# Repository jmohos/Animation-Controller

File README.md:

# Animation-Controller
Robotic Animation Control Project

## VS Code Workspace
Use the workspace file when building, uploading, or monitoring the serial port so VS Code opens the full project with PlatformIO settings.

Prerequisites:
- Visual Studio Code
- PlatformIO IDE extension for VS Code (installs toolchains and dependencies on first build)
- Teensy 4.1 USB drivers for your OS (Windows: Teensyduino installer includes the driver)
- A known-good USB data cable for upload and serial monitoring

1. Open VS Code.
2. File -> Open Workspace from File...
3. Select `2025_Animation_Controller.code-workspace` in the repo root.
4. Use the PlatformIO toolbar to Build, Upload, and Monitor the serial port.
5. First build: PlatformIO will download toolchains and libraries. Select the Teensy serial port and use 115200 baud for the monitor.

## Display
The control station software currently targets the ILI9341 240x320 display only.
Other display drivers and build options have been removed.

## Functional System Description
To faciliate the orchestration of an animated robotic system, an animation controller assembly is needed.  This controller takes on the responsibility of monitoring and controlling all participating show elements in a synchronized manner.  A typical parade float can consist of a dozen animated features that each require managed motion across potentially multiple dimensions.  By having a single control node manage all of the animated features, all of the elements can be synchronized into a cohesive show where coordinated motion can add to the quality of the performance. This project covers the design of such an animation controller.

The key high level requirements include:
* A single control assembly that can operate on 12VDC power input.
* Has a user interface for the local animation operator to monitor the overall animation, control the selected animation process, manually control elements and edit the animation sequence.
* Can control a series of robotic endpoints using one CAN bus plus up to 7 full-duplex serial ports (Serial1 pins 0/1 reserved for CAN).
* Robotic endpoints can be either motion, light or sound controllers.
* The motion control endpoints will include the BasicMicro Roboclaw controllers which can control either 1 or 2 motors via a single serial interface.
* RoboClaw controllers must be configured for Packet Serial mode at 115200 baud.
* Future options for motion control endpoints will include options to manage stepper motors, servos, solenoids and hydraulic valves.
* Future options for light control will include endpoints to manage DMX-based light controllers.
* Future options for sound control will include endpoints that can receive commands to play audio tracks.
* Animation sequences shall be stored in a portable animation sequence file that contains the time-based steps for each animation endpoint.
* Animation sequences are stored on the animation controller SD card.

## Endpoint and Animation Files
Endpoint configuration lives in `/endpoints.csv` on the SD card. The animation sequence lives in `/animation.csv` and only contains a `[sequence]` section. The animation file defines a single looping animation with a maximum duration of 5 minutes (300000 ms).

Endpoint config schema (CSV columns, in order):
1. `endpoint_id` - 1-based endpoint index.
2. `type` - `ROBOCLAW`, `MKS_SERVO`, `REV_FRC_CAN`, `JOE_SERVO_SERIAL`, or `JOE_SERVO_CAN`.
3. `address` - Device address or CAN ID (hex allowed, e.g. `0x80`).
4. `enabled` - `1` or `0`.
5. `position_min` - Minimum allowed position (degrees if `pulses_per_rev > 0`, else device units).
6. `position_max` - Maximum allowed position (degrees if `pulses_per_rev > 0`, else device units).
7. `velocity_min` - Minimum allowed velocity (deg/s if `pulses_per_rev > 0`, else device units).
8. `velocity_max` - Maximum allowed velocity (deg/s if `pulses_per_rev > 0`, else device units).
9. `accel_min` - Minimum allowed acceleration (deg/s² if `pulses_per_rev > 0`, else device units).
10. `accel_max` - Maximum allowed acceleration (deg/s² if `pulses_per_rev > 0`, else device units).
11. `serial_port` - Interface index (0=CAN on pins 0/1, 1-7=RS422 serial ports).
12. `motor` - RoboClaw motor channel (`1` or `2`), `0` when unused.
13. `pulses_per_rev` - Pulses per revolution for engineering units (0 = device units mode, >0 enables degrees/deg/s units).
14. `home_offset` - Offset from limit switch to zero position in pulses.
15. `home_direction` - Homing direction (0=negative, 1=positive).
16. `has_limit_switch` - Limit switch present (0=no, 1=yes).

Sequence schema (CSV columns, in order):
1. `time_ms` - Integer milliseconds from 0 to 300000.
2. `endpoint_id` - 1-based endpoint index.
3. `position` - Target position.
4. `velocity` - Target velocity.
5. `accel` - Target acceleration.
6. `mode` (optional) - `pos` (default) or `vel` to issue a velocity-only command.

Example:
```
# endpoints.csv
# endpoint_id,type,address,enabled,position_min,position_max,velocity_min,velocity_max,accel_min,accel_max,serial_port,motor,pulses_per_rev,home_offset,home_direction,has_limit_switch
1,MKS_SERVO,0x00000001,1,-360,360,0,100,0,50,0,0,16384,0,0,0
2,ROBOCLAW,0x00000080,1,-360,360,0,100,0,50,1,1,4096,0,0,0

# animation.csv
[sequence]
# time_ms,endpoint_id,position,velocity,accel,mode
0,1,0,800,250,pos
2000,1,1000,800,250,pos
```

Notes:
- Lines starting with `#` are comments and ignored.
- The animation loops at the largest `time_ms` found, capped at 300000 ms.
- `velocity` and `accel` are required on every row for consistency.
- Serial1 (pins 0/1) is reserved for the CAN transceiver and is not available for RS422 endpoints.
- The CAN bus is initialized at 500 kbps.
- Default SD card files live in `Software/Animation_Control_Station/sd_defaults`.

## Known Issues

### CAN Bus Interrupt Mode
The CAN bus currently operates in **polled mode only**. Interrupt mode causes system crashes on Teensy 4.1. This is a known issue with the FlexCAN_T4 library or hardware timing.

**Workaround**: The code uses `CANBUS_USE_POLLING` (defined by default). The `CanBus::events()` method explicitly reads the mailbox each loop iteration. Performance impact is minimal at 500 kbps.

**Status**: Under investigation. Do not enable `CANBUS_USE_INTERRUPTS`.

### EEPROM Configuration Migration
Upgrading from firmware versions with config version < 7 will reset endpoint configuration to defaults. After upgrading, reload your `/endpoints.csv` file from SD card.

## Troubleshooting

### CAN Bus Issues
- **Symptom**: MKS Servo not responding
- **Check**: Verify CAN transceiver connected to Teensy pins 0 (CAN_TX) and 1 (CAN_RX)
- **Check**: Verify 500 kbps bitrate match on all devices
- **Check**: CAN bus requires 120Ω termination resistors at both ends
- **Debug**: Use console command `can status` to check error counters

### SD Card Not Detected
- **Symptom**: "SD card not ready" message on boot
- **Check**: SD card must be formatted as FAT32
- **Check**: Verify `/endpoints.csv` and `/animation.csv` exist in root directory
- **Check**: Use known-good SD card (some cards have compatibility issues)
- **Recovery**: Copy files from `sd_defaults/` directory

### RoboClaw Not Responding
- **Symptom**: No motion from RoboClaw-controlled motors
- **Check**: RoboClaw must be in **Packet Serial mode** at 115200 baud
- **Check**: Verify RS422 serial connections (TX/RX not swapped)
- **Check**: Verify RoboClaw address matches `endpoints.csv` configuration
- **Debug**: Use console command `rc status <endpoint_id>` to read encoder values

### Encoder Position Drift
- **Symptom**: Position drifts over time or after power cycle
- **Solution**: Perform homing sequence with `home <endpoint_id>` command
- **Check**: Verify limit switches are properly wired and configured
- **Check**: Verify `has_limit_switch=1` in endpoints.csv for endpoints that support homing

## Engineering Units System

Starting with firmware version 7, the system supports **engineering units** for position, velocity, and acceleration commands. This allows you to specify motion in degrees and degrees per second regardless of the underlying hardware.

### Configuration

Set the `pulses_per_rev` field in `/endpoints.csv` to enable engineering units for an endpoint:

```csv
endpoint_id,type,address,...,pulses_per_rev,home_offset,home_direction,has_limit_switch
1,MKS_SERVO,0x00000001,...,16384,0,0,0
```

**Pulses Per Revolution Values**:
- **MKS Servo**: 16384 pulses/revolution (encoder subdivisions, default)
- **RoboClaw**: Depends on encoder resolution and gearing (e.g., 4096 for common encoders)
- **Custom**: Calculate as: `encoder_lines * 4 * gearing_ratio * microstepping`

**Important**: The `pulses_per_rev` value must account for:
1. Encoder resolution (quadrature count = 4× encoder lines)
2. Microstepping (if applicable)
3. Gearing between motor shaft and final output shaft

### Units

When `pulses_per_rev > 0`, all position/velocity/acceleration values use engineering units:

| Parameter | Units | Range | Notes |
|-----------|-------|-------|-------|
| **Position** | degrees | ±2,000,000° | Multi-revolution support (±5,555 revs) |
| **Velocity** | deg/s | 0-360 deg/s typical | Converts to RPM for MKS, counts/s for RoboClaw |
| **Acceleration** | deg/s² | 0-100 deg/s² typical | Converts to device-specific scale |

### Examples

**360° rotation at 60 RPM**:
```csv
[sequence]
time_ms,endpoint_id,position,velocity,accel,mode
0,1,0,360,50,pos
1000,1,360,360,50,pos
```

**Continuous rotation**:
```csv
0,1,0,180,50,pos
2000,1,720,180,50,pos     # 2 full revolutions
4000,1,1440,180,50,pos    # 4 full revolutions
```

### Backwards Compatibility

To maintain device units (old behavior), set `pulses_per_rev = 0` in endpoints.csv. The system will pass position/velocity/acceleration values directly to the hardware without conversion.

### Homing and Zero Position

The system supports auto-homing with limit switches:

1. Set `has_limit_switch=1` in endpoints.csv
2. Set `home_direction` (0=negative, 1=positive)
3. Set `home_offset` (distance in pulses from limit to zero position)
4. Run homing: Console command `home <endpoint_id>` or use Homing screen

After homing, all position commands are relative to the zero position.

## Console Commands Reference

Connect via USB serial at 115200 baud. Commands are case-sensitive.

### SD Card Commands
- `sd dir` - List files on SD card
- `sd read <path>` - Display file contents
- `sd test` - Test SD card read/write performance

### Configuration Commands
- `config save` - Save current configuration to EEPROM
- `config load endpoints` - Reload `/endpoints.csv` from SD card
- `config show` - Display current configuration
- `factory reset` - Reset to factory defaults (WARNING: erases config)

### Endpoint Commands
- `ep list` - Show all endpoint configurations
- `ep show <id>` - Show detailed config for endpoint
- `ep enable <id>` - Enable endpoint
- `ep disable <id>` - Disable endpoint

### Sequence Commands
- `seq load` - Reload `/animation.csv` from SD card
- `seq info` - Display sequence statistics (event count, duration)

### RoboClaw Commands
- `rc status <endpoint_id>` - Read encoder position and speed

### CAN Bus Commands
- `can status` - Display CAN bus health (error counters, fault state)

### Homing Commands
- `home <endpoint_id>` - Start auto-homing sequence for endpoint

### System Commands
- `reboot` - Restart controller
- `help` - Display command list

### Hardware - Overall System
The animator controller is the heart of a complete animation deployment used for shows like parade floats and general animatronic performances.  Such shows require multiple robotic actuators to work independently or in concert to perform synchronized motion, light and sound sequences.

A deployed system would typically consist of:
* Robotic power system to provide electrical power to the animation controller, motion controllers, lights and sound systems.
* A robotic animation controller to manage the entire show process.  This controller would contain a scripted set of animations to orchestrate across all of the animated elements.
* A set of robotic endpoints that the animation controller manages.  Each of these endpoints communicates with the animation controller via a serial link.  Endpoints report their status and receive control commands from the animation controller.  A typical command is to move an actuator to a given position at a given max speed and given max acceleration.  It can also command things like light patterns and sound triggers.
* The animation controller has a user interface where the animation operator can select from recorded animation patters, enable play/stop of the patterns or edit and manually control the endpoints.

### Hardware - Animation Controller
The animation controller assembly consists of the following:
* A Teensy 4.1 microcontroller board to manage the entire system.
* A 12VDC power input port with DC:DC converters to 5VDC and 3.3VDC.
* The power conversion stage has reverse polarity protection and has transient suppression above 18v.
* An LCD display connected to the Teensy 4.1 primary SPI.  It is a ILI9341 based display with 240x320 pixel resolution.
* A SX1509 IO expander board from Sparkfun connected to the Teensy 4.1 to provide 8 pins of button inputs and 8 pins of LED outputs.  By using this I2C device we free up the other pins of the Teensy 4.1.
* Two 10K Ohm potentiometers attached to Teensy 4.1 analog inputs.  These physical knobs allow the operator to input desired speed and acceleration parameters. The inputs are scaled from 0.0 to 100.0 with deadbands at the bottom and top to ensure we can reach the limits with the potentiometer.
* A rotary encoder jog wheel connected to the Teensy 4.1 to provide a physical positioning input by the operator.  It uses a two input quadrature encoder to count the incremental steps either forward or backwards.
* A set of buttons to provide menu navigation for the menu system displayed on the screen.  The five buttons include up, down, left, right and Ok.  This is implemented using a 5 way tactile button located next to the display.
* A set of three context sensitive buttons with LED backlights.  These buttons are located below the display to align with a set of hot-key displays at the bottom of the screen guiding you on what the three buttons currently do when pressed.  The buttons are Red (left), Yellow (center), and Green (right).
* The backlights for the Red, Yellow and Green buttons are controlled by the SX1509 IO expander outputs.  The output of the SX1509 outputs 8-15 are wired to an ULN2803 driver chip that switches 12V selectively to the LED outputs.
* The LED outputs can be commanded to be off, on or blink with a selectable on and off time to create unique patterns.
* The Teensy 4.1 serial ports 2-8 are wired to a set of 7 connectors with VCC, Ground, RX and TX each.  These connectors mate with a set of 7 RS422, full-duplex serial converters that wire to each of the 7 remote actuator stations.
* An SD card slot on the Teensy 4.1 will be used for storage of the animation sequences.
* The Teensy 4.1 FLASH EEPROM will be used to store configuration settings like the number animation endpoints, their modes and their enables.
* The animation controller shall operate in a series of operating states that can include:
  * BOOT - System initializing and restoring EEPROM config and last configured SD card animation sequence into RAM.
  * MANUAL - The UI is focused on manually manipulating a single animation endpoint at a time.  The Red button is used to toggle between play and pause.  The yellow button, while held pressed, is used to select the endpoint number using the jog wheel.  The green button is used to trigger a move command to the endpoint.  The jog wheel, when yellow is not held, is used to adjust target position.  The speed and accel knobs are used to set the max speed and acceleration factor for the move.
  * AUTO - The UI is focused on displaying what time index in the animation sequence we are at, what the motion activity is.  If the red button is toggled, it will switch between play and pause mode.  While paused, the job wheel can be used to manually cycle through the animation sequence time and thus advance each channel in concert to allow for forward and backwards slow motion playback.
  * EDIT - TBD, operators will be able to edit new animation sequences for each endpoint using the speed, accel and jog wheel along with the red, yellow and green buttons to cue the next time marker and endpoint position.
* Animation playback shall use methods to smooth the playback transitions between animation timestamps to prevent the motion from being jerky.

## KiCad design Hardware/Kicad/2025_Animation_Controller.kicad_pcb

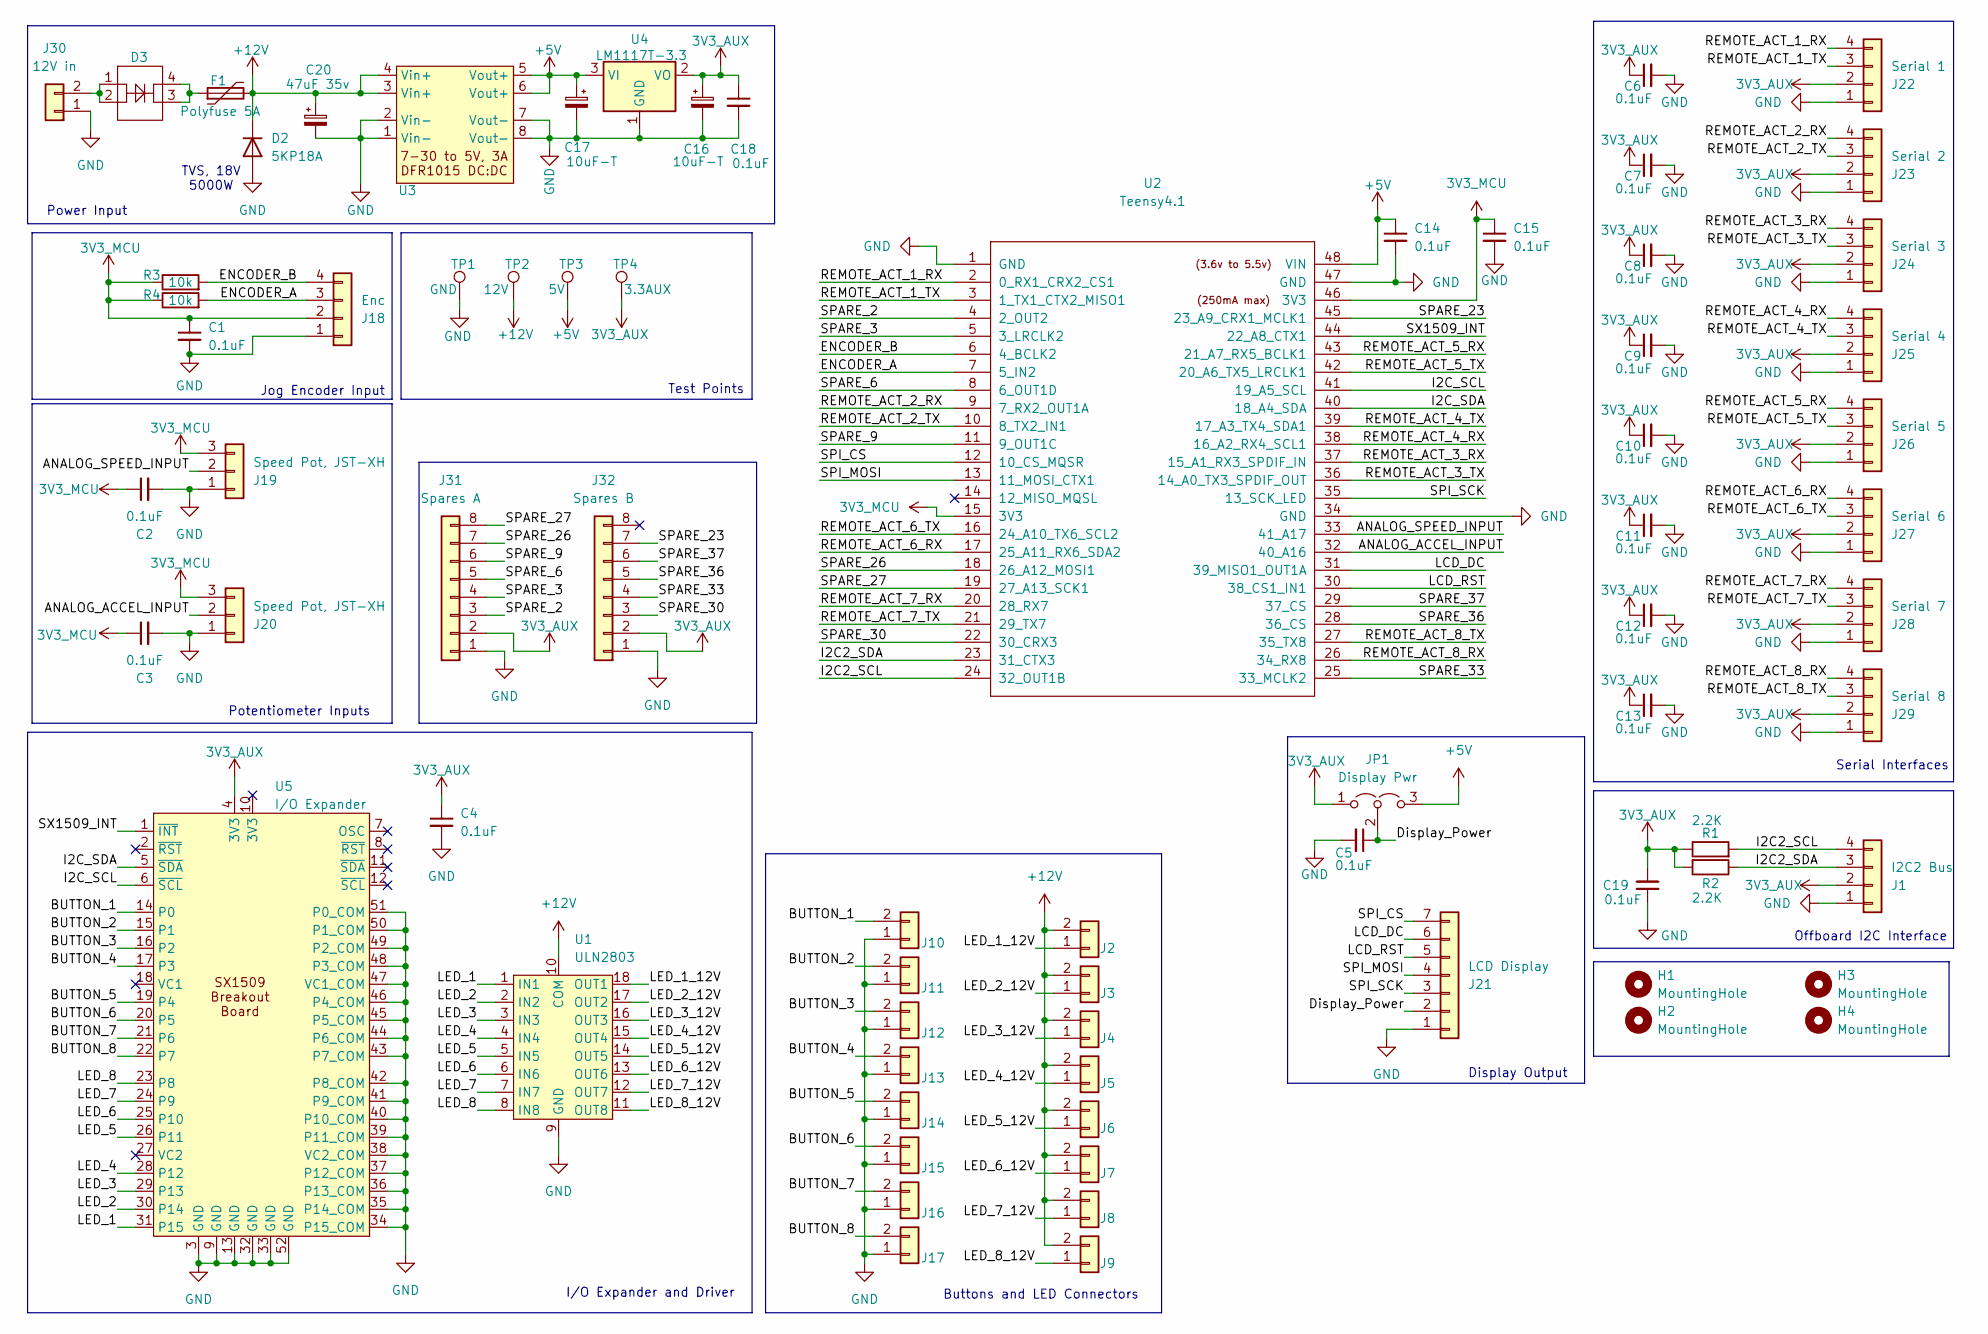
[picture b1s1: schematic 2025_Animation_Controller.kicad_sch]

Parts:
C1, C2, C3, C4, C5, C6, C7, C8, C9, C10, C11, C12, C13, C14, C15, C18, C19: 0.1uF; C_Disc_D5.1mm_W3.2mm_P5.00mm
C16, C17: 10uF-T; CP_Radial_Tantal_D5.5mm_P2.50mm
C20: 47uF 35v; CP_Radial_D8.0mm_P3.50mm
D2: 5KP18A; D_P600_R-6_P12.70mm_Horizontal
D3: Ideal Diode; Ideal_Diode_AGM403A
F1: Polyfuse 5A; Fuse_Littelfuse_395Series
H1, H2, H3, H4: MountingHole; MountingHole_3.2mm_M3
J1: I2C2 Bus; JST_XH_B4B-XH-A_1x04_P2.50mm_Vertical
J2, J3, J4, J5, J6, J7, J8, J9, J10, J11, J12, J13, J14, J15, J16, J17: Conn_01x02; JST_XH_B2B-XH-A_1x02_P2.50mm_Vertical
J18: Enc; JST_XH_B4B-XH-A_1x04_P2.50mm_Vertical
J19, J20: Speed Pot, JST-XH; JST_XH_B3B-XH-A_1x03_P2.50mm_Vertical
J21: LCD Display; JST_XH_B7B-XH-A_1x07_P2.50mm_Vertical
J22: Serial 1; JST_XH_B4B-XH-A_1x04_P2.50mm_Vertical
J23: Serial 2; JST_XH_B4B-XH-A_1x04_P2.50mm_Vertical
J24: Serial 3; JST_XH_B4B-XH-A_1x04_P2.50mm_Vertical
J25: Serial 4; JST_XH_B4B-XH-A_1x04_P2.50mm_Vertical
J26: Serial 5; JST_XH_B4B-XH-A_1x04_P2.50mm_Vertical
J27: Serial 6; JST_XH_B4B-XH-A_1x04_P2.50mm_Vertical
J28: Serial 7; JST_XH_B4B-XH-A_1x04_P2.50mm_Vertical
J29: Serial 8; JST_XH_B4B-XH-A_1x04_P2.50mm_Vertical
J30: 12V in; JST_XH_B2B-XH-AM_1x02_P2.50mm_Vertical
J31: Spares A; JST_XH_B8B-XH-A_1x08_P2.50mm_Vertical
J32: Spares B; JST_XH_B8B-XH-A_1x08_P2.50mm_Vertical
JP1: Display Pwr; PinHeader_1x03_P2.54mm_Vertical
R1, R2: 2.2K; R_Axial_DIN0207_L6.3mm_D2.5mm_P10.16mm_Horizontal
R3, R4: 10k; R_Axial_DIN0207_L6.3mm_D2.5mm_P10.16mm_Horizontal
TP1: GND; TestPoint_Plated_Hole_D2.0mm
TP2: 12V; TestPoint_Plated_Hole_D2.0mm
TP3: 5V; TestPoint_Plated_Hole_D2.0mm
TP4: 3.3AUX; TestPoint_Plated_Hole_D2.0mm
U1: ULN2803; ULN2803_Breakout_Board
U2: Teensy4.1; Teensy41
U3: DFR1015; DCDC_Converter_DFR1015
U4: LM1117T-3.3; TO-220-3_Vertical
U5: I/O Expander; SX1509_Breakout_Board

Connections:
3V3_AUX: C4.1, C6.1, C7.1, C8.1, C9.1, C10.1, C11.1, C12.1, C13.1, C16.1, C18.1, C19.2, J1.2, J22.2, J23.2, J24.2, J25.2, J26.2, J27.2, J28.2, J29.2, J31.2, J32.2, JP1.1 (A), R1.1, R2.2, TP4.1, U4.2 (VO), U5.4 (3V3)
3V3_MCU: C1.1, C2.1, C3.1, C15.1, J18.2, J19.3, J20.3, R3.1, R4.1, U2.15 (3V3), U2.46 (3V3)
+5V: C14.1, C17.1, JP1.3 (B), TP3.1, U2.48 (VIN), U3.5 (Vout+), U3.6 (Vout+), U4.3 (VI)
+12V: C20.1, D2.1 (K), F1.2, J2.2, J3.2, J4.2, J5.2, J6.2, J7.2, J8.2, J9.2, TP2.1, U1.10 (COM), U3.3 (Vin+), U3.4 (Vin+)
/ANALOG_ACCEL_INPUT: J20.2, U2.32 (40_A16)
/ANALOG_SPEED_INPUT: J19.2, U2.33 (41_A17)
/BUTTON_1: J10.2, U5.14 (P0)
/BUTTON_2: J11.2, U5.15 (P1)
/BUTTON_3: J12.2, U5.16 (P2)
/BUTTON_4: J13.2, U5.17 (P3)
/BUTTON_5: J14.2, U5.19 (P4)
/BUTTON_6: J15.2, U5.20 (P5)
/BUTTON_7: J16.2, U5.21 (P6)
/BUTTON_8: J17.2, U5.22 (P7)
/Display_Power: C5.1, J21.2, JP1.2 (C)
/ENCODER_A: J18.3, R4.2, U2.7 (5_IN2)
/ENCODER_B: J18.4, R3.2, U2.6 (4_BCLK2)
/I2C2_SCL: J1.4, R1.2, U2.24 (32_OUT1B)
/I2C2_SDA: J1.3, R2.1, U2.23 (31_CTX3)
/I2C_SCL: U2.41 (19_A5_SCL), U5.6 (~SCL)
/I2C_SDA: U2.40 (18_A4_SDA), U5.5 (~SDA)
/LCD_DC: J21.6, U2.31 (39_MISO1_OUT1A)
/LCD_RST: J21.5, U2.30 (38_CS1_IN1)
/LED_1: U1.1 (IN1), U5.31 (P15)
/LED_1_12V: J2.1, U1.18 (OUT1)
/LED_2: U1.2 (IN2), U5.30 (P14)
/LED_2_12V: J3.1, U1.17 (OUT2)
/LED_3: U1.3 (IN3), U5.29 (P13)
/LED_3_12V: J4.1, U1.16 (OUT3)
/LED_4: U1.4 (IN4), U5.28 (P12)
/LED_4_12V: J5.1, U1.15 (OUT4)
/LED_5: U1.5 (IN5), U5.26 (P11)
/LED_5_12V: J6.1, U1.14 (OUT5)
/LED_6: U1.6 (IN6), U5.25 (P10)
/LED_6_12V: J7.1, U1.13 (OUT6)
/LED_7: U1.7 (IN7), U5.24 (P9)
/LED_7_12V: J8.1, U1.12 (OUT7)
/LED_8: U1.8 (IN8), U5.23 (P8)
/LED_8_12V: J9.1, U1.11 (OUT8)
/REMOTE_ACT_1_RX: J22.4, U2.2 (0_RX1_CRX2_CS1)
/REMOTE_ACT_1_TX: J22.3, U2.3 (1_TX1_CTX2_MISO1)
/REMOTE_ACT_2_RX: J23.4, U2.9 (7_RX2_OUT1A)
/REMOTE_ACT_2_TX: J23.3, U2.10 (8_TX2_IN1)
/REMOTE_ACT_3_RX: J24.4, U2.37 (15_A1_RX3_SPDIF_IN)
/REMOTE_ACT_3_TX: J24.3, U2.36 (14_A0_TX3_SPDIF_OUT)
/REMOTE_ACT_4_RX: J25.4, U2.38 (16_A2_RX4_SCL1)
/REMOTE_ACT_4_TX: J25.3, U2.39 (17_A3_TX4_SDA1)
/REMOTE_ACT_5_RX: J26.4, U2.43 (21_A7_RX5_BCLK1)
/REMOTE_ACT_5_TX: J26.3, U2.42 (20_A6_TX5_LRCLK1)
/REMOTE_ACT_6_RX: J27.4, U2.17 (25_A11_RX6_SDA2)
/REMOTE_ACT_6_TX: J27.3, U2.16 (24_A10_TX6_SCL2)
/REMOTE_ACT_7_RX: J28.4, U2.20 (28_RX7)
/REMOTE_ACT_7_TX: J28.3, U2.21 (29_TX7)
/REMOTE_ACT_8_RX: J29.4, U2.26 (34_RX8)
/REMOTE_ACT_8_TX: J29.3, U2.27 (35_TX8)
/SPARE_2: J31.3, U2.4 (2_OUT2)
/SPARE_3: J31.4, U2.5 (3_LRCLK2)
/SPARE_6: J31.5, U2.8 (6_OUT1D)
/SPARE_9: J31.6, U2.11 (9_OUT1C)
/SPARE_23: J32.7, U2.45 (23_A9_CRX1_MCLK1)
/SPARE_26: J31.7, U2.18 (26_A12_MOSI1)
/SPARE_27: J31.8, U2.19 (27_A13_SCK1)
/SPARE_30: J32.3, U2.22 (30_CRX3)
/SPARE_33: J32.4, U2.25 (33_MCLK2)
/SPARE_36: J32.5, U2.28 (36_CS)
/SPARE_37: J32.6, U2.29 (37_CS)
/SPI_CS: J21.7, U2.12 (10_CS_MQSR)
/SPI_MOSI: J21.4, U2.13 (11_MOSI_CTX1)
/SPI_SCK: J21.3, U2.35 (13_SCK_LED)
/SX1509_INT: U2.44 (22_A8_CTX1), U5.1 (~INT)
GND: C1.2, C2.2, C3.2, C4.2, C5.2, C6.2, C7.2, C8.2, C9.2, C10.2, C11.2, C12.2, C13.2, C14.2, C15.2, C16.2, C17.2, C18.2, C19.1, C20.2, D2.2 (A), J1.1, J10.1, J11.1, J12.1, J13.1, J14.1, J15.1, J16.1, J17.1, J18.1, J19.1, J20.1, J21.1, J22.1, J23.1, J24.1, J25.1, J26.1, J27.1, J28.1, J29.1, J30.1, J31.1, J32.1, TP1.1, U1.9 (GND), U2.1 (GND), U2.34 (GND), U2.47 (GND), U3.1 (Vin-), U3.2 (Vin-), U3.7 (Vout-), U3.8 (Vout-), U4.1 (GND), U5.3 (GND), U5.9 (GND), U5.13 (GND), U5.32 (GND), U5.33 (GND), U5.34 (P15_COM), U5.35 (P14_COM), U5.36 (P13_COM), U5.37 (P12_COM), U5.38 (VC2_COM), U5.39 (P11_COM), U5.40 (P10_COM), U5.41 (P9_COM), U5.42 (P8_COM), U5.43 (P7_COM), U5.44 (P6_COM), U5.45 (P5_COM), U5.46 (P4_COM), U5.47 (VC1_COM), U5.48 (P3_COM), U5.49 (P2_COM), U5.50 (P1_COM), U5.51 (P0_COM), U5.52 (GND)
unnamed: D3.3, D3.4, F1.1
unnamed: D3.1, D3.2, J30.2

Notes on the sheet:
Offboard I2C Interface
Display Output
Buttons and LED Connectors
Potentiometer Inputs
TVS, 18V 5000W
Serial Interfaces
Test Points
Jog Encoder Input
Power Input
I/O Expander and Driver

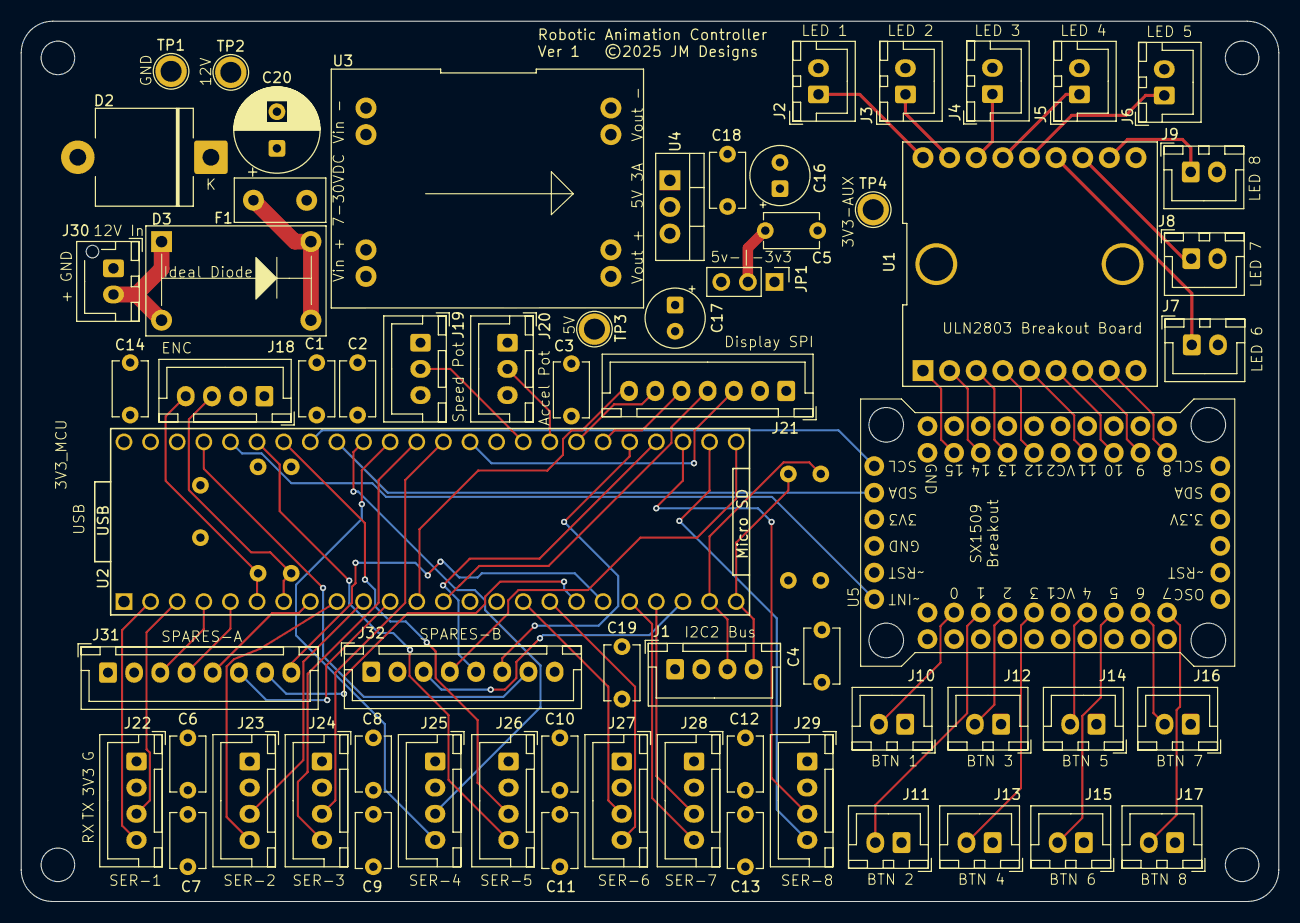
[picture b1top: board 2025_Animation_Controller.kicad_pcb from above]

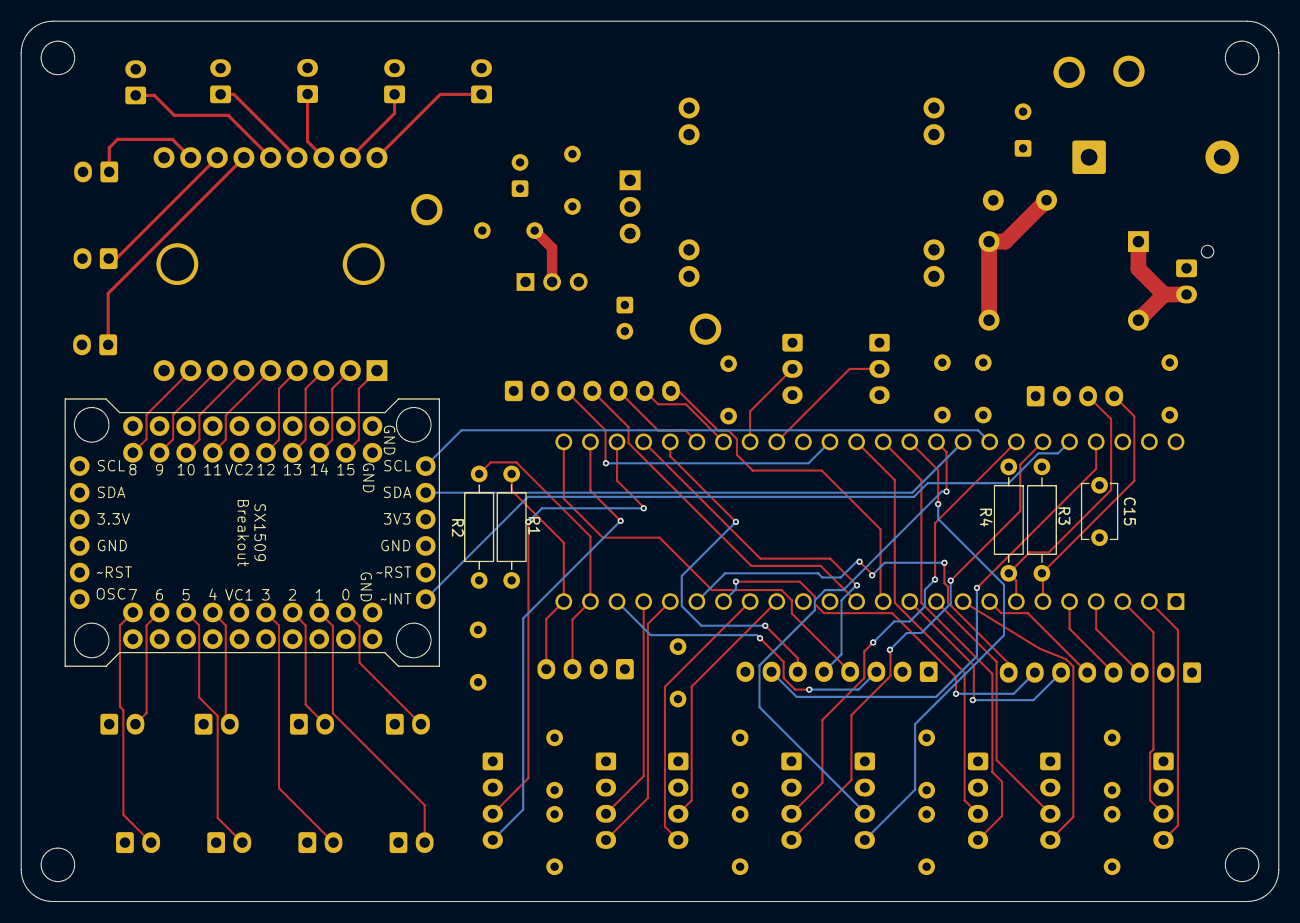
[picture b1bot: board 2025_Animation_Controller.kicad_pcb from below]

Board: 4 copper layers, 120.0 x 84.0 mm, 73 parts (5 on the bottom side), 73 nets.

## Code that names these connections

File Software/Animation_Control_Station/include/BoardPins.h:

#pragma once
#include <Arduino.h>

// LCD: ILI9341 240x320
static constexpr uint8_t PIN_LCD_CS  = 10;
static constexpr uint8_t PIN_LCD_DC  = 39;
static constexpr uint8_t PIN_LCD_RST = 38;
static constexpr uint8_t PIN_LCD_BL  = 255;

// I2C: SX1509
static constexpr uint8_t PIN_I2C_SDA    = 18;
static constexpr uint8_t PIN_I2C_SCL    = 19;
static constexpr uint8_t PIN_SX1509_INT = 22;

enum class SXPin : uint8_t {
  SX_BUTTON_1 = 0,
  SX_BUTTON_2 = 1,
  SX_BUTTON_3 = 2,
  SX_BUTTON_4 = 3,
  SX_BUTTON_5 = 4,
  SX_BUTTON_6 = 5,
  SX_BUTTON_7 = 6,
  SX_BUTTON_8 = 7,
  SX_LED_1 = 8,
  SX_LED_2 = 9,
  SX_LED_3 = 10,
  SX_LED_4 = 11,
  SX_LED_5 = 12,
  SX_LED_6 = 13,
  SX_LED_7 = 14,
  SX_LED_8 = 15,
  COUNT
};

static constexpr uint8_t SX1509_PIN_COUNT = static_cast<uint8_t>(SXPin::COUNT);

// Analog pots
static constexpr uint8_t PIN_POT_SPEED = A16;
static constexpr uint8_t PIN_POT_ACCEL = A17;

// Quadrature jog encoder
static constexpr uint8_t PIN_ENC_A = 5;
static constexpr uint8_t PIN_ENC_B = 4;

// ---------------- RS422 ports ----------------
struct Rs422PortPins {
    uint8_t rx;
    uint8_t tx;
};

static constexpr Rs422PortPins ROBOCLAW_PORT_PINS[8] = {
    /*1*/ { 0,  1},
    /*2*/ { 7,  8},
    /*3*/ {15, 14},
    /*4*/ {16, 17},
    /*5*/ {21, 20},
    /*6*/ {25, 24},
    /*7*/ {28, 29},
    /*8*/ {34, 35},
};

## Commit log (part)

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2025-12-31 Initial commit to repo
2025-12-31 Initial upload of hardware and docs
2025-12-31 Commit initial pcd design files and updated docs.
2026-01-09 Prep for production PCB V1
2026-01-11 Cleaned up LED mapping.
2026-01-11 Ignore large media files
2026-01-11 Reduce to single display option and separate UI elements.
2026-01-11 Prep for major SW changes to implement control modes.
2026-01-12 Actual RoboClaw coms working.
2026-01-19 First working edit revision.
2026-01-25 First working CAN version. Must use polled CAN bus, interrupts still cause crash.
2026-01-27 Switched to rotation angle for position control and velocity.
2026-04-01 Switch from DMX to RS485.

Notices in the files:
Hardware/Kicad/2025_Animation_Controller.kicad_pcb:
Ver 1 ©2025 JM Designs
